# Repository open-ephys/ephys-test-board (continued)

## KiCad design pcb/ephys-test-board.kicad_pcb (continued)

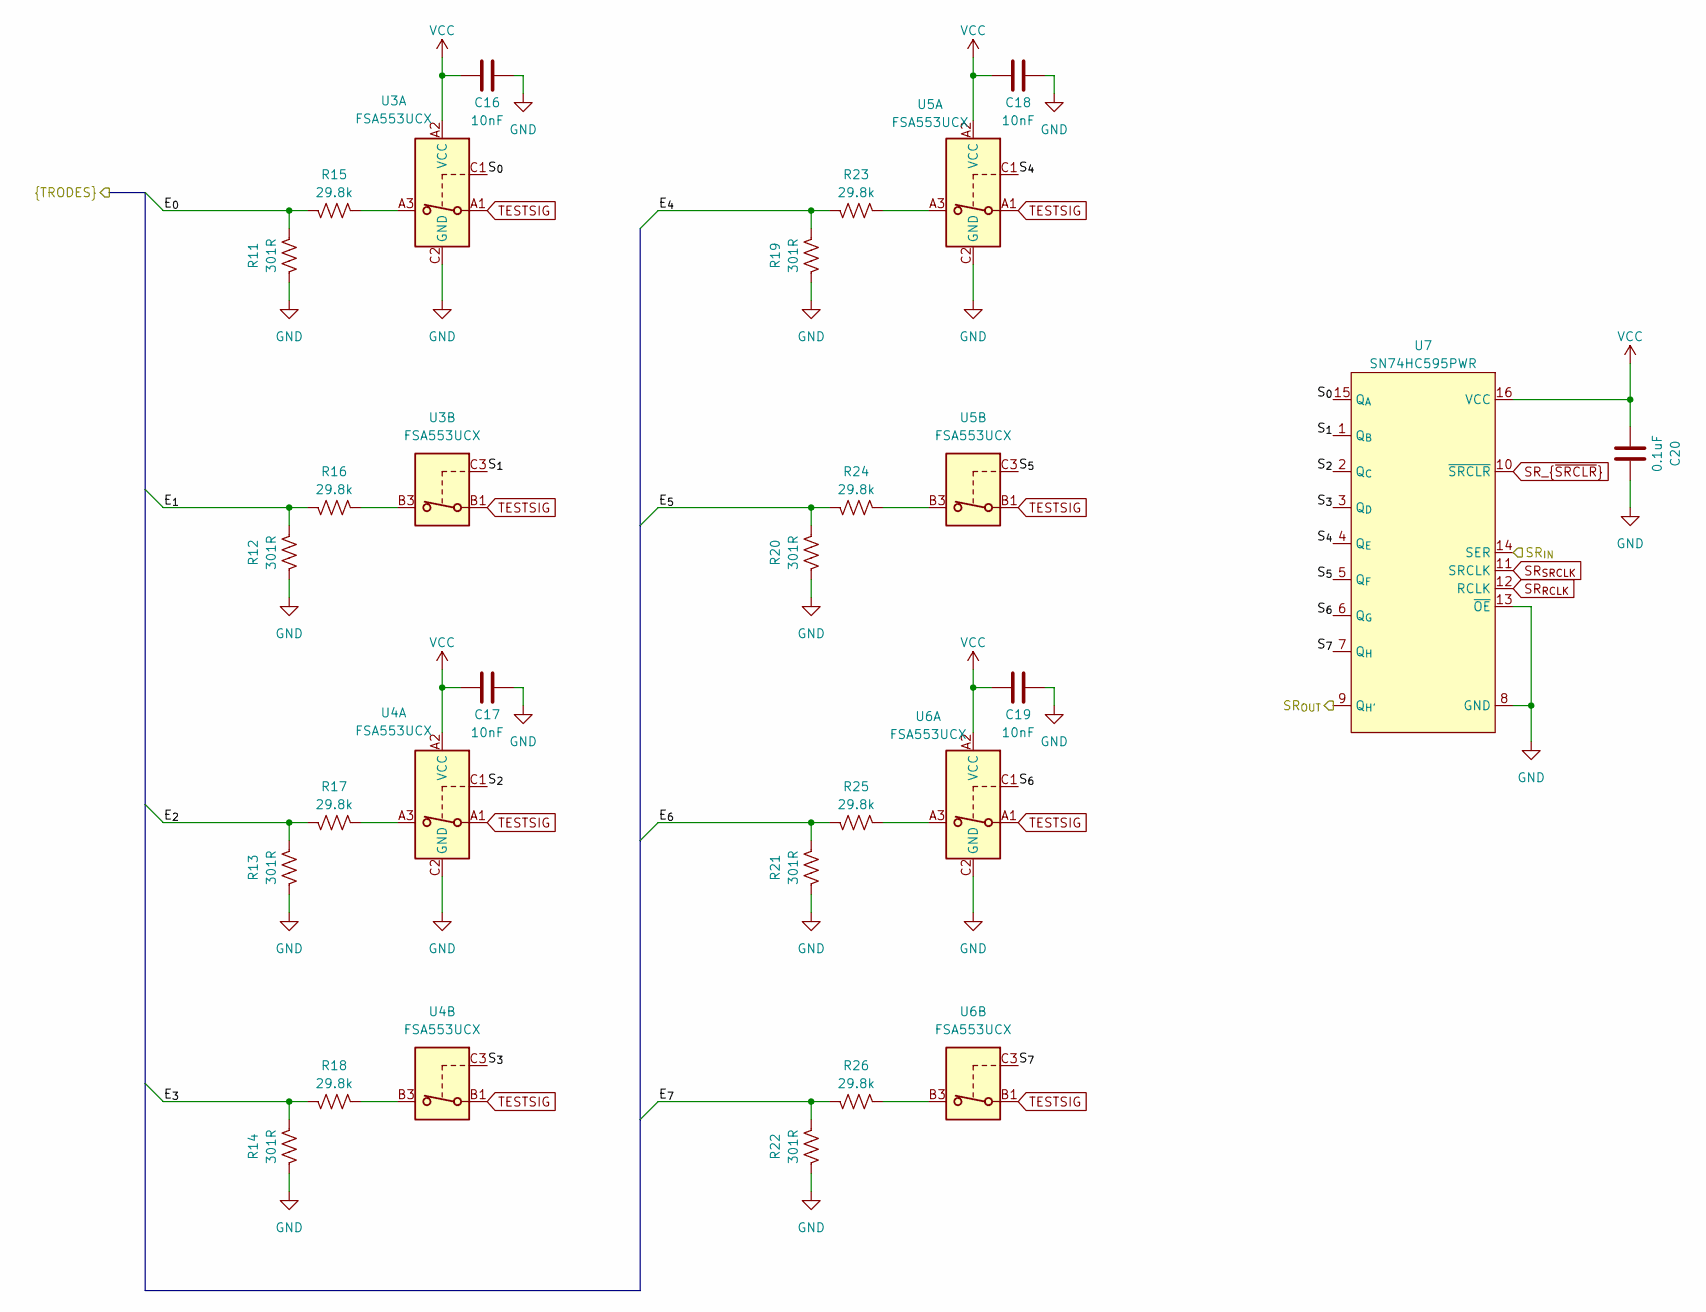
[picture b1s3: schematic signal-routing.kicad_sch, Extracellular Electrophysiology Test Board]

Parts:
C16, C17, C18, C19: 10nF; C_0402_1005Metric; Voltage 50V; MPN GRM155R71E103KA01D; LCSC C60133
C20: 0.1uF; C_0402_1005Metric; Voltage 25V; MPN C1005X7R1E104K050BB; LCSC C105883
R11, R12, R13, R14, R19, R20, R21, R22: 301R; R_0402_1005Metric; Tolerance 0.1%; MPN RT0402BRD07301RL; LCSC C705632
R15, R16, R17, R18, R23, R24, R25, R26: 29.8k; R_0402_1005Metric; Tolerance 0.1%; MPN RN73R1ETTP2982B25; LCSC C2506693
U3, U4, U5, U6: FSA553UCX; ONSEMI_567SV_WLCSP9-3x3-1.215x1.385x0.581mm-P0.4mm; MPN FSA553UCX; LCSC C605183
U7: SN74HC595PWR; TSSOP-16_4.4x5mm_P0.65mm; MPN SN74HC595PWR; LCSC C273642

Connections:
/Headstage IO/B0.E_{0}: R11.1, R15.2; also elsewhere on the board
/Headstage IO/B0.E_{1}: R12.1, R16.2; also elsewhere on the board
/Headstage IO/B0.E_{2}: R13.1, R17.2; also elsewhere on the board
/Headstage IO/B0.E_{3}: R14.1, R18.2; also elsewhere on the board
/Headstage IO/B0.E_{4}: R19.1, R23.2; also elsewhere on the board
/Headstage IO/B0.E_{5}: R20.1, R24.2; also elsewhere on the board
/Headstage IO/B0.E_{6}: R21.1, R25.2; also elsewhere on the board
/Headstage IO/B0.E_{7}: R22.1, R26.2; also elsewhere on the board
/MCU/SR_{SER}: U7.14 (SER); also elsewhere on the board
/Signal Routing 0/SR_{OUT}: U7.9 (Q_{H'}); also elsewhere on the board
/Signal Routing 0/S_{0}: U3.C1, U7.15 (Q_{A})
/Signal Routing 0/S_{1}: U3.C3, U7.1 (Q_{B})
/Signal Routing 0/S_{2}: U4.C1, U7.2 (Q_{C})
/Signal Routing 0/S_{3}: U4.C3, U7.3 (Q_{D})
/Signal Routing 0/S_{4}: U5.C1, U7.4 (Q_{E})
/Signal Routing 0/S_{5}: U5.C3, U7.5 (Q_{F})
/Signal Routing 0/S_{6}: U6.C1, U7.6 (Q_{G})
/Signal Routing 0/S_{7}: U6.C3, U7.7 (Q_{H})
GND: C16.2, C17.2, C18.2, C19.2, C20.2, R11.2, R12.2, R13.2, R14.2, R19.2, R20.2, R21.2, R22.2, U3.C2 (GND), U4.C2 (GND), U5.C2 (GND), U6.C2 (GND), U7.8 (GND), U7.13 (~OE); also elsewhere on the board
unnamed: R15.1, U3.A3
unnamed: R16.1, U3.B3
unnamed: R17.1, U4.A3
unnamed: R18.1, U4.B3
unnamed: R23.1, U5.A3
unnamed: R24.1, U5.B3
unnamed: R25.1, U6.A3
unnamed: R26.1, U6.B3
SR_{RCLK}: U7.12 (RCLK); also elsewhere on the board
SR_{SRCLK}: U7.11 (SRCLK); also elsewhere on the board
SR_{~SRCLR}: U7.10 (~SRCLR); also elsewhere on the board
TESTSIG: U3.A1, U3.B1, U4.A1, U4.B1, U5.A1, U5.B1, U6.A1, U6.B1; also elsewhere on the board
VCC: C16.1, C17.1, C18.1, C19.1, C20.1, U3.A2 (VCC), U4.A2 (VCC), U5.A2 (VCC), U6.A2 (VCC), U7.16 (VCC); also elsewhere on the board

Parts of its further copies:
C21, C22, C23, C24, C26, C27, C28, C29, C31, C32, C33, C34, C36, C37, C38, C39, C41, C42, C43, C44, C46, C47, C48, C49, C51, C52, C53, C54, C56, C57, C58, C59, C61, C62, C63, C64, C66, C67, C68, C69, C71, C72, C73, C74, C76, C77, C78, C79, C81, C82, C83, C84, C86, C87, C88, C89, C91, C92, C93, C94: 10nF; C_0402_1005Metric; Voltage 50V; MPN GRM155R71E103KA01D; LCSC C60133
C25, C30, C35, C40, C45, C50, C55, C60, C65, C70, C75, C80, C85, C90, C95: 0.1uF; C_0402_1005Metric; Voltage 25V; MPN C1005X7R1E104K050BB; LCSC C105883
R27, R28, R29, R30, R35, R36, R37, R38, R43, R44, R45, R46, R51, R52, R53, R54, R59, R60, R61, R62, R67, R68, R69, R70, R75, R76, R77, R78, R83, R84, R85, R86, R91, R92, R93, R94, R99, R100, R101, R102, R107, R108, R109, R110, R115, R116, R117, R118, R123, R124, R125, R126, R131, R132, R133, R134, R139, R140, R141, R142, R147, R148, R149, R150, R155, R156, R157, R158, R163, R164, R165, R166, R171, R172, R173, R174, R179, R180, R181, R182, R187, R188, R189, R190, R195, R196, R197, R198, R203, R204, R205, R206, R211, R212, R213, R214, R219, R220, R221, R222, R227, R228, R229, R230, R235, R236, R237, R238, R243, R244, R245, R246, R251, R252, R253, R254, R259, R260, R261, R262: 301R; R_0402_1005Metric; Tolerance 0.1%; MPN RT0402BRD07301RL; LCSC C705632
R31, R32, R33, R34, R39, R40, R41, R42, R47, R48, R49, R50, R55, R56, R57, R58, R63, R64, R65, R66, R71, R72, R73, R74, R79, R80, R81, R82, R87, R88, R89, R90, R95, R96, R97, R98, R103, R104, R105, R106, R111, R112, R113, R114, R119, R120, R121, R122, R127, R128, R129, R130, R135, R136, R137, R138, R143, R144, R145, R146, R151, R152, R153, R154, R159, R160, R161, R162, R167, R168, R169, R170, R175, R176, R177, R178, R183, R184, R185, R186, R191, R192, R193, R194, R199, R200, R201, R202, R207, R208, R209, R210, R215, R216, R217, R218, R223, R224, R225, R226, R231, R232, R233, R234, R239, R240, R241, R242, R247, R248, R249, R250, R255, R256, R257, R258, R263, R264, R265, R266: 29.8k; R_0402_1005Metric; Tolerance 0.1%; MPN RN73R1ETTP2982B25; LCSC C2506693
U8, U9, U10, U11, U13, U14, U15, U16, U18, U19, U20, U21, U23, U24, U25, U26, U28, U29, U30, U31, U33, U34, U35, U36, U38, U39, U40, U41, U43, U44, U45, U46, U48, U49, U50, U51, U53, U54, U55, U56, U58, U59, U60, U61, U63, U64, U65, U66, U68, U69, U70, U71, U73, U74, U75, U76, U78, U79, U80, U81: FSA553UCX; ONSEMI_567SV_WLCSP9-3x3-1.215x1.385x0.581mm-P0.4mm; MPN FSA553UCX; LCSC C605183
U12, U17, U22, U27, U32, U37, U42, U47, U52, U57, U62, U67, U72, U77, U82: SN74HC595PWR; TSSOP-16_4.4x5mm_P0.65mm; MPN SN74HC595PWR; LCSC C273642

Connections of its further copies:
/Headstage IO/B1.E_{0}: R27.1, R31.2; also elsewhere on the board
/Headstage IO/B1.E_{1}: R28.1, R32.2; also elsewhere on the board
/Headstage IO/B1.E_{2}: R29.1, R33.2; also elsewhere on the board
/Headstage IO/B1.E_{3}: R30.1, R34.2; also elsewhere on the board
/Headstage IO/B1.E_{4}: R35.1, R39.2; also elsewhere on the board
/Headstage IO/B1.E_{5}: R36.1, R40.2; also elsewhere on the board
/Headstage IO/B1.E_{6}: R37.1, R41.2; also elsewhere on the board
/Headstage IO/B1.E_{7}: R38.1, R42.2; also elsewhere on the board
/Headstage IO/B2.E_{0}: R43.1, R47.2; also elsewhere on the board
/Headstage IO/B2.E_{1}: R44.1, R48.2; also elsewhere on the board
/Headstage IO/B2.E_{2}: R45.1, R49.2; also elsewhere on the board
/Headstage IO/B2.E_{3}: R46.1, R50.2; also elsewhere on the board
/Headstage IO/B2.E_{4}: R51.1, R55.2; also elsewhere on the board
/Headstage IO/B2.E_{5}: R52.1, R56.2; also elsewhere on the board
/Headstage IO/B2.E_{6}: R53.1, R57.2; also elsewhere on the board
/Headstage IO/B2.E_{7}: R54.1, R58.2; also elsewhere on the board
/Headstage IO/B3.E_{0}: R59.1, R63.2; also elsewhere on the board
/Headstage IO/B3.E_{1}: R60.1, R64.2; also elsewhere on the board
/Headstage IO/B3.E_{2}: R61.1, R65.2; also elsewhere on the board
/Headstage IO/B3.E_{3}: R62.1, R66.2; also elsewhere on the board
/Headstage IO/B3.E_{4}: R67.1, R71.2; also elsewhere on the board
/Headstage IO/B3.E_{5}: R68.1, R72.2; also elsewhere on the board
/Headstage IO/B3.E_{6}: R69.1, R73.2; also elsewhere on the board
/Headstage IO/B3.E_{7}: R70.1, R74.2; also elsewhere on the board
/Headstage IO/B4.E_{0}: R75.1, R79.2; also elsewhere on the board
/Headstage IO/B4.E_{1}: R76.1, R80.2; also elsewhere on the board
/Headstage IO/B4.E_{2}: R77.1, R81.2; also elsewhere on the board
/Headstage IO/B4.E_{3}: R78.1, R82.2; also elsewhere on the board
/Headstage IO/B4.E_{4}: R83.1, R87.2; also elsewhere on the board
/Headstage IO/B4.E_{5}: R84.1, R88.2; also elsewhere on the board
/Headstage IO/B4.E_{6}: R85.1, R89.2; also elsewhere on the board
/Headstage IO/B4.E_{7}: R86.1, R90.2; also elsewhere on the board
/Headstage IO/B5.E_{0}: R91.1, R95.2; also elsewhere on the board
/Headstage IO/B5.E_{1}: R92.1, R96.2; also elsewhere on the board
/Headstage IO/B5.E_{2}: R93.1, R97.2; also elsewhere on the board
/Headstage IO/B5.E_{3}: R94.1, R98.2; also elsewhere on the board
/Headstage IO/B5.E_{4}: R99.1, R103.2; also elsewhere on the board
/Headstage IO/B5.E_{5}: R100.1, R104.2; also elsewhere on the board
/Headstage IO/B5.E_{6}: R101.1, R105.2; also elsewhere on the board
/Headstage IO/B5.E_{7}: R102.1, R106.2; also elsewhere on the board
/Headstage IO/B6.E_{0}: R107.1, R111.2; also elsewhere on the board
/Headstage IO/B6.E_{1}: R108.1, R112.2; also elsewhere on the board
/Headstage IO/B6.E_{2}: R109.1, R113.2; also elsewhere on the board
/Headstage IO/B6.E_{3}: R110.1, R114.2; also elsewhere on the board
/Headstage IO/B6.E_{4}: R115.1, R119.2; also elsewhere on the board
/Headstage IO/B6.E_{5}: R116.1, R120.2; also elsewhere on the board
/Headstage IO/B6.E_{6}: R117.1, R121.2; also elsewhere on the board
/Headstage IO/B6.E_{7}: R118.1, R122.2; also elsewhere on the board
/Headstage IO/B7.E_{0}: R123.1, R127.2; also elsewhere on the board
/Headstage IO/B7.E_{1}: R124.1, R128.2; also elsewhere on the board
/Headstage IO/B7.E_{2}: R125.1, R129.2; also elsewhere on the board
/Headstage IO/B7.E_{3}: R126.1, R130.2; also elsewhere on the board
/Headstage IO/B7.E_{4}: R131.1, R135.2; also elsewhere on the board
/Headstage IO/B7.E_{5}: R132.1, R136.2; also elsewhere on the board
/Headstage IO/B7.E_{6}: R133.1, R137.2; also elsewhere on the board
/Headstage IO/B7.E_{7}: R134.1, R138.2; also elsewhere on the board
/Headstage IO/B8.E_{0}: R139.1, R143.2; also elsewhere on the board
/Headstage IO/B8.E_{1}: R140.1, R144.2; also elsewhere on the board
/Headstage IO/B8.E_{2}: R141.1, R145.2; also elsewhere on the board
/Headstage IO/B8.E_{3}: R142.1, R146.2; also elsewhere on the board
/Headstage IO/B8.E_{4}: R147.1, R151.2; also elsewhere on the board
/Headstage IO/B8.E_{5}: R148.1, R152.2; also elsewhere on the board
/Headstage IO/B8.E_{6}: R149.1, R153.2; also elsewhere on the board
/Headstage IO/B8.E_{7}: R150.1, R154.2; also elsewhere on the board
/Headstage IO/B9.E_{0}: R155.1, R159.2; also elsewhere on the board
/Headstage IO/B9.E_{1}: R156.1, R160.2; also elsewhere on the board
/Headstage IO/B9.E_{2}: R157.1, R161.2; also elsewhere on the board
/Headstage IO/B9.E_{3}: R158.1, R162.2; also elsewhere on the board
/Headstage IO/B9.E_{4}: R163.1, R167.2; also elsewhere on the board
/Headstage IO/B9.E_{5}: R164.1, R168.2; also elsewhere on the board
/Headstage IO/B9.E_{6}: R165.1, R169.2; also elsewhere on the board
/Headstage IO/B9.E_{7}: R166.1, R170.2; also elsewhere on the board
/Headstage IO/B10.E_{0}: R171.1, R175.2; also elsewhere on the board
/Headstage IO/B10.E_{1}: R172.1, R176.2; also elsewhere on the board
/Headstage IO/B10.E_{2}: R173.1, R177.2; also elsewhere on the board
/Headstage IO/B10.E_{3}: R174.1, R178.2; also elsewhere on the board
/Headstage IO/B10.E_{4}: R179.1, R183.2; also elsewhere on the board
/Headstage IO/B10.E_{5}: R180.1, R184.2; also elsewhere on the board
/Headstage IO/B10.E_{6}: R181.1, R185.2; also elsewhere on the board
/Headstage IO/B10.E_{7}: R182.1, R186.2; also elsewhere on the board
/Headstage IO/B11.E_{0}: R187.1, R191.2; also elsewhere on the board
/Headstage IO/B11.E_{1}: R188.1, R192.2; also elsewhere on the board
/Headstage IO/B11.E_{2}: R189.1, R193.2; also elsewhere on the board
/Headstage IO/B11.E_{3}: R190.1, R194.2; also elsewhere on the board
/Headstage IO/B11.E_{4}: R195.1, R199.2; also elsewhere on the board
/Headstage IO/B11.E_{5}: R196.1, R200.2; also elsewhere on the board
/Headstage IO/B11.E_{6}: R197.1, R201.2; also elsewhere on the board
/Headstage IO/B11.E_{7}: R198.1, R202.2; also elsewhere on the board
/Headstage IO/B12.E_{0}: R203.1, R207.2; also elsewhere on the board
/Headstage IO/B12.E_{1}: R204.1, R208.2; also elsewhere on the board
/Headstage IO/B12.E_{2}: R205.1, R209.2; also elsewhere on the board
/Headstage IO/B12.E_{3}: R206.1, R210.2; also elsewhere on the board
/Headstage IO/B12.E_{4}: R211.1, R215.2; also elsewhere on the board
/Headstage IO/B12.E_{5}: R212.1, R216.2; also elsewhere on the board
/Headstage IO/B12.E_{6}: R213.1, R217.2; also elsewhere on the board
/Headstage IO/B12.E_{7}: R214.1, R218.2; also elsewhere on the board
/Headstage IO/B13.E_{0}: R219.1, R223.2; also elsewhere on the board
/Headstage IO/B13.E_{1}: R220.1, R224.2; also elsewhere on the board
/Headstage IO/B13.E_{2}: R221.1, R225.2; also elsewhere on the board
/Headstage IO/B13.E_{3}: R222.1, R226.2; also elsewhere on the board
/Headstage IO/B13.E_{4}: R227.1, R231.2; also elsewhere on the board
/Headstage IO/B13.E_{5}: R228.1, R232.2; also elsewhere on the board
/Headstage IO/B13.E_{6}: R229.1, R233.2; also elsewhere on the board
/Headstage IO/B13.E_{7}: R230.1, R234.2; also elsewhere on the board
/Headstage IO/B14.E_{0}: R235.1, R239.2; also elsewhere on the board
/Headstage IO/B14.E_{1}: R236.1, R240.2; also elsewhere on the board
/Headstage IO/B14.E_{2}: R237.1, R241.2; also elsewhere on the board
/Headstage IO/B14.E_{3}: R238.1, R242.2; also elsewhere on the board
/Headstage IO/B14.E_{4}: R243.1, R247.2; also elsewhere on the board
/Headstage IO/B14.E_{5}: R244.1, R248.2; also elsewhere on the board
/Headstage IO/B14.E_{6}: R245.1, R249.2; also elsewhere on the board
/Headstage IO/B14.E_{7}: R246.1, R250.2; also elsewhere on the board
/Headstage IO/B15.E_{0}: R251.1, R255.2; also elsewhere on the board
/Headstage IO/B15.E_{1}: R252.1, R256.2; also elsewhere on the board
/Headstage IO/B15.E_{2}: R253.1, R257.2; also elsewhere on the board
/Headstage IO/B15.E_{3}: R254.1, R258.2; also elsewhere on the board
/Headstage IO/B15.E_{4}: R259.1, R263.2; also elsewhere on the board
/Headstage IO/B15.E_{5}: R260.1, R264.2; also elsewhere on the board
/Headstage IO/B15.E_{6}: R261.1, R265.2; also elsewhere on the board
/Headstage IO/B15.E_{7}: R262.1, R266.2; also elsewhere on the board
/Signal Routing 0/SR_{OUT}: U12.14 (SER); also elsewhere on the board
/Signal Routing 1/SR_{OUT}: U12.9 (Q_{H'}), U17.14 (SER)
/Signal Routing 1/S_{0}: U8.C1, U12.15 (Q_{A})
/Signal Routing 1/S_{1}: U8.C3, U12.1 (Q_{B})
/Signal Routing 1/S_{2}: U9.C1, U12.2 (Q_{C})
/Signal Routing 1/S_{3}: U9.C3, U12.3 (Q_{D})
/Signal Routing 1/S_{4}: U10.C1, U12.4 (Q_{E})
/Signal Routing 1/S_{5}: U10.C3, U12.5 (Q_{F})
/Signal Routing 1/S_{6}: U11.C1, U12.6 (Q_{G})
/Signal Routing 1/S_{7}: U11.C3, U12.7 (Q_{H})
/Signal Routing 2/SR_{OUT}: U17.9 (Q_{H'}), U22.14 (SER)
/Signal Routing 2/S_{0}: U13.C1, U17.15 (Q_{A})
/Signal Routing 2/S_{1}: U13.C3, U17.1 (Q_{B})
/Signal Routing 2/S_{2}: U14.C1, U17.2 (Q_{C})
/Signal Routing 2/S_{3}: U14.C3, U17.3 (Q_{D})
/Signal Routing 2/S_{4}: U15.C1, U17.4 (Q_{E})
/Signal Routing 2/S_{5}: U15.C3, U17.5 (Q_{F})
/Signal Routing 2/S_{6}: U16.C1, U17.6 (Q_{G})
/Signal Routing 2/S_{7}: U16.C3, U17.7 (Q_{H})
/Signal Routing 3/SR_{OUT}: U22.9 (Q_{H'}), U27.14 (SER)
/Signal Routing 3/S_{0}: U18.C1, U22.15 (Q_{A})
/Signal Routing 3/S_{1}: U18.C3, U22.1 (Q_{B})
/Signal Routing 3/S_{2}: U19.C1, U22.2 (Q_{C})
/Signal Routing 3/S_{3}: U19.C3, U22.3 (Q_{D})
/Signal Routing 3/S_{4}: U20.C1, U22.4 (Q_{E})
/Signal Routing 3/S_{5}: U20.C3, U22.5 (Q_{F})
/Signal Routing 3/S_{6}: U21.C1, U22.6 (Q_{G})
/Signal Routing 3/S_{7}: U21.C3, U22.7 (Q_{H})
/Signal Routing 4/SR_{OUT}: U27.9 (Q_{H'}), U32.14 (SER)
/Signal Routing 4/S_{0}: U23.C1, U27.15 (Q_{A})
/Signal Routing 4/S_{1}: U23.C3, U27.1 (Q_{B})
/Signal Routing 4/S_{2}: U24.C1, U27.2 (Q_{C})
/Signal Routing 4/S_{3}: U24.C3, U27.3 (Q_{D})
/Signal Routing 4/S_{4}: U25.C1, U27.4 (Q_{E})
/Signal Routing 4/S_{5}: U25.C3, U27.5 (Q_{F})
/Signal Routing 4/S_{6}: U26.C1, U27.6 (Q_{G})
/Signal Routing 4/S_{7}: U26.C3, U27.7 (Q_{H})
/Signal Routing 5/SR_{OUT}: U32.9 (Q_{H'}), U37.14 (SER)
/Signal Routing 5/S_{0}: U28.C1, U32.15 (Q_{A})
/Signal Routing 5/S_{1}: U28.C3, U32.1 (Q_{B})
/Signal Routing 5/S_{2}: U29.C1, U32.2 (Q_{C})
/Signal Routing 5/S_{3}: U29.C3, U32.3 (Q_{D})
/Signal Routing 5/S_{4}: U30.C1, U32.4 (Q_{E})
/Signal Routing 5/S_{5}: U30.C3, U32.5 (Q_{F})
/Signal Routing 5/S_{6}: U31.C1, U32.6 (Q_{G})
/Signal Routing 5/S_{7}: U31.C3, U32.7 (Q_{H})
/Signal Routing 6/SR_{OUT}: U37.9 (Q_{H'}), U42.14 (SER)
/Signal Routing 6/S_{0}: U33.C1, U37.15 (Q_{A})
/Signal Routing 6/S_{1}: U33.C3, U37.1 (Q_{B})
/Signal Routing 6/S_{2}: U34.C1, U37.2 (Q_{C})
/Signal Routing 6/S_{3}: U34.C3, U37.3 (Q_{D})
/Signal Routing 6/S_{4}: U35.C1, U37.4 (Q_{E})
/Signal Routing 6/S_{5}: U35.C3, U37.5 (Q_{F})
/Signal Routing 6/S_{6}: U36.C1, U37.6 (Q_{G})
/Signal Routing 6/S_{7}: U36.C3, U37.7 (Q_{H})
/Signal Routing 7/SR_{OUT}: U42.9 (Q_{H'}), U47.14 (SER)
/Signal Routing 7/S_{0}: U38.C1, U42.15 (Q_{A})
/Signal Routing 7/S_{1}: U38.C3, U42.1 (Q_{B})
/Signal Routing 7/S_{2}: U39.C1, U42.2 (Q_{C})
/Signal Routing 7/S_{3}: U39.C3, U42.3 (Q_{D})
/Signal Routing 7/S_{4}: U40.C1, U42.4 (Q_{E})
/Signal Routing 7/S_{5}: U40.C3, U42.5 (Q_{F})
/Signal Routing 7/S_{6}: U41.C1, U42.6 (Q_{G})
/Signal Routing 7/S_{7}: U41.C3, U42.7 (Q_{H})
/Signal Routing 8/SR_{OUT}: U47.9 (Q_{H'}), U52.14 (SER)
/Signal Routing 8/S_{0}: U43.C1, U47.15 (Q_{A})
/Signal Routing 8/S_{1}: U43.C3, U47.1 (Q_{B})
/Signal Routing 8/S_{2}: U44.C1, U47.2 (Q_{C})
/Signal Routing 8/S_{3}: U44.C3, U47.3 (Q_{D})
/Signal Routing 8/S_{4}: U45.C1, U47.4 (Q_{E})
/Signal Routing 8/S_{5}: U45.C3, U47.5 (Q_{F})
/Signal Routing 8/S_{6}: U46.C1, U47.6 (Q_{G})
/Signal Routing 8/S_{7}: U46.C3, U47.7 (Q_{H})
/Signal Routing 9/S_{0}: U48.C1, U52.15 (Q_{A})
/Signal Routing 9/S_{1}: U48.C3, U52.1 (Q_{B})
/Signal Routing 9/S_{2}: U49.C1, U52.2 (Q_{C})
/Signal Routing 9/S_{3}: U49.C3, U52.3 (Q_{D})
/Signal Routing 9/S_{4}: U50.C1, U52.4 (Q_{E})
/Signal Routing 9/S_{5}: U50.C3, U52.5 (Q_{F})
/Signal Routing 9/S_{6}: U51.C1, U52.6 (Q_{G})
/Signal Routing 9/S_{7}: U51.C3, U52.7 (Q_{H})
/Signal Routing 10/SR_{IN}: U52.9 (Q_{H'}), U57.14 (SER)
/Signal Routing 10/SR_{OUT}: U57.9 (Q_{H'}), U62.14 (SER)
/Signal Routing 10/S_{0}: U53.C1, U57.15 (Q_{A})
/Signal Routing 10/S_{1}: U53.C3, U57.1 (Q_{B})
/Signal Routing 10/S_{2}: U54.C1, U57.2 (Q_{C})
/Signal Routing 10/S_{3}: U54.C3, U57.3 (Q_{D})
/Signal Routing 10/S_{4}: U55.C1, U57.4 (Q_{E})
/Signal Routing 10/S_{5}: U55.C3, U57.5 (Q_{F})
/Signal Routing 10/S_{6}: U56.C1, U57.6 (Q_{G})
/Signal Routing 10/S_{7}: U56.C3, U57.7 (Q_{H})
/Signal Routing 11/SR_{OUT}: U62.9 (Q_{H'}), U67.14 (SER)
/Signal Routing 11/S_{0}: U58.C1, U62.15 (Q_{A})
/Signal Routing 11/S_{1}: U58.C3, U62.1 (Q_{B})
/Signal Routing 11/S_{2}: U59.C1, U62.2 (Q_{C})
/Signal Routing 11/S_{3}: U59.C3, U62.3 (Q_{D})
/Signal Routing 11/S_{4}: U60.C1, U62.4 (Q_{E})
/Signal Routing 11/S_{5}: U60.C3, U62.5 (Q_{F})
/Signal Routing 11/S_{6}: U61.C1, U62.6 (Q_{G})
/Signal Routing 11/S_{7}: U61.C3, U62.7 (Q_{H})
/Signal Routing 12/SR_{OUT}: U67.9 (Q_{H'}), U72.14 (SER)
/Signal Routing 12/S_{0}: U63.C1, U67.15 (Q_{A})
/Signal Routing 12/S_{1}: U63.C3, U67.1 (Q_{B})
/Signal Routing 12/S_{2}: U64.C1, U67.2 (Q_{C})
/Signal Routing 12/S_{3}: U64.C3, U67.3 (Q_{D})
/Signal Routing 12/S_{4}: U65.C1, U67.4 (Q_{E})
/Signal Routing 12/S_{5}: U65.C3, U67.5 (Q_{F})
/Signal Routing 12/S_{6}: U66.C1, U67.6 (Q_{G})
/Signal Routing 12/S_{7}: U66.C3, U67.7 (Q_{H})
/Signal Routing 13/SR_{OUT}: U72.9 (Q_{H'}), U77.14 (SER)
/Signal Routing 13/S_{0}: U68.C1, U72.15 (Q_{A})
/Signal Routing 13/S_{1}: U68.C3, U72.1 (Q_{B})
/Signal Routing 13/S_{2}: U69.C1, U72.2 (Q_{C})
/Signal Routing 13/S_{3}: U69.C3, U72.3 (Q_{D})
/Signal Routing 13/S_{4}: U70.C1, U72.4 (Q_{E})
/Signal Routing 13/S_{5}: U70.C3, U72.5 (Q_{F})
/Signal Routing 13/S_{6}: U71.C1, U72.6 (Q_{G})
/Signal Routing 13/S_{7}: U71.C3, U72.7 (Q_{H})
/Signal Routing 14/SR_{OUT}: U77.9 (Q_{H'}), U82.14 (SER)
/Signal Routing 14/S_{0}: U73.C1, U77.15 (Q_{A})
/Signal Routing 14/S_{1}: U73.C3, U77.1 (Q_{B})
/Signal Routing 14/S_{2}: U74.C1, U77.2 (Q_{C})
/Signal Routing 14/S_{3}: U74.C3, U77.3 (Q_{D})
/Signal Routing 14/S_{4}: U75.C1, U77.4 (Q_{E})
/Signal Routing 14/S_{5}: U75.C3, U77.5 (Q_{F})
/Signal Routing 14/S_{6}: U76.C1, U77.6 (Q_{G})
/Signal Routing 14/S_{7}: U76.C3, U77.7 (Q_{H})
/Signal Routing 15/SR_{OUT}: U82.9 (Q_{H'})
/Signal Routing 15/S_{0}: U78.C1, U82.15 (Q_{A})
/Signal Routing 15/S_{1}: U78.C3, U82.1 (Q_{B})
/Signal Routing 15/S_{2}: U79.C1, U82.2 (Q_{C})
/Signal Routing 15/S_{3}: U79.C3, U82.3 (Q_{D})
/Signal Routing 15/S_{4}: U80.C1, U82.4 (Q_{E})
/Signal Routing 15/S_{5}: U80.C3, U82.5 (Q_{F})
/Signal Routing 15/S_{6}: U81.C1, U82.6 (Q_{G})
/Signal Routing 15/S_{7}: U81.C3, U82.7 (Q_{H})
GND: C21.2, C22.2, C23.2, C24.2, C25.2, C26.2, C27.2, C28.2, C29.2, C30.2, C31.2, C32.2, C33.2, C34.2, C35.2, C36.2, C37.2, C38.2, C39.2, C40.2, C41.2, C42.2, C43.2, C44.2, C45.2, C46.2, C47.2, C48.2, C49.2, C50.2, C51.2, C52.2, C53.2, C54.2, C55.2, C56.2, C57.2, C58.2, C59.2, C60.2, C61.2, C62.2, C63.2, C64.2, C65.2, C66.2, C67.2, C68.2, C69.2, C70.2, C71.2, C72.2, C73.2, C74.2, C75.2, C76.2, C77.2, C78.2, C79.2, C80.2, C81.2, C82.2, C83.2, C84.2, C85.2, C86.2, C87.2, C88.2, C89.2, C90.2, C91.2, C92.2, C93.2, C94.2, C95.2, R27.2, R28.2, R29.2, R30.2, R35.2, R36.2, R37.2, R38.2, R43.2, R44.2, R45.2, R46.2, R51.2, R52.2, R53.2, R54.2, R59.2, R60.2, R61.2, R62.2, R67.2, R68.2, R69.2, R70.2, R75.2, R76.2, R77.2, R78.2, R83.2, R84.2, R85.2, R86.2, R91.2, R92.2, R93.2, R94.2, R99.2, R100.2, R101.2, R102.2, R107.2, R108.2, R109.2, R110.2, R115.2, R116.2, R117.2, R118.2, R123.2, R124.2, R125.2, R126.2, R131.2, R132.2, R133.2, R134.2, R139.2, R140.2, R141.2, R142.2, R147.2, R148.2, R149.2, R150.2, R155.2, R156.2, R157.2, R158.2, R163.2, R164.2, R165.2, R166.2, R171.2, R172.2, R173.2, R174.2, R179.2, R180.2, R181.2, R182.2, R187.2, R188.2, R189.2, R190.2, R195.2, R196.2, R197.2, R198.2, R203.2, R204.2, R205.2, R206.2, R211.2, R212.2, R213.2, R214.2, R219.2, R220.2, R221.2, R222.2, R227.2, R228.2, R229.2, R230.2, R235.2, R236.2, R237.2, R238.2, R243.2, R244.2, R245.2, R246.2, R251.2, R252.2, R253.2, R254.2, R259.2, R260.2, R261.2, R262.2, U8.C2 (GND), U9.C2 (GND), U10.C2 (GND), U11.C2 (GND), U12.8 (GND), U12.13 (~OE), U13.C2 (GND), U14.C2 (GND), U15.C2 (GND), U16.C2 (GND), U17.8 (GND), U17.13 (~OE), U18.C2 (GND), U19.C2 (GND), U20.C2 (GND), U21.C2 (GND), U22.8 (GND), U22.13 (~OE), U23.C2 (GND), U24.C2 (GND), U25.C2 (GND), U26.C2 (GND), U27.8 (GND), U27.13 (~OE), U28.C2 (GND), U29.C2 (GND), U30.C2 (GND), U31.C2 (GND), U32.8 (GND), U32.13 (~OE), U33.C2 (GND), U34.C2 (GND), U35.C2 (GND), U36.C2 (GND), U37.8 (GND), U37.13 (~OE), U38.C2 (GND), U39.C2 (GND), U40.C2 (GND), U41.C2 (GND), U42.8 (GND), U42.13 (~OE), U43.C2 (GND), U44.C2 (GND), U45.C2 (GND), U46.C2 (GND), U47.8 (GND), U47.13 (~OE), U48.C2 (GND), U49.C2 (GND), U50.C2 (GND), U51.C2 (GND), U52.8 (GND), U52.13 (~OE), U53.C2 (GND), U54.C2 (GND), U55.C2 (GND), U56.C2 (GND), U57.8 (GND), U57.13 (~OE), U58.C2 (GND), U59.C2 (GND), U60.C2 (GND), U61.C2 (GND), U62.8 (GND), U62.13 (~OE), U63.C2 (GND), U64.C2 (GND), U65.C2 (GND), U66.C2 (GND), U67.8 (GND), U67.13 (~OE), U68.C2 (GND), U69.C2 (GND), U70.C2 (GND), U71.C2 (GND), U72.8 (GND), U72.13 (~OE), U73.C2 (GND), U74.C2 (GND), U75.C2 (GND), U76.C2 (GND), U77.8 (GND), U77.13 (~OE), U78.C2 (GND), U79.C2 (GND), U80.C2 (GND), U81.C2 (GND), U82.8 (GND), U82.13 (~OE); also elsewhere on the board
unnamed: R31.1, U8.A3
unnamed: R32.1, U8.B3
unnamed: R33.1, U9.A3
unnamed: R34.1, U9.B3
unnamed: R39.1, U10.A3
unnamed: R40.1, U10.B3
unnamed: R41.1, U11.A3
unnamed: R42.1, U11.B3
unnamed: R47.1, U13.A3
unnamed: R48.1, U13.B3
unnamed: R49.1, U14.A3
unnamed: R50.1, U14.B3
unnamed: R55.1, U15.A3
unnamed: R56.1, U15.B3
unnamed: R57.1, U16.A3
unnamed: R58.1, U16.B3
unnamed: R63.1, U18.A3
unnamed: R64.1, U18.B3
unnamed: R65.1, U19.A3
unnamed: R66.1, U19.B3
unnamed: R71.1, U20.A3
unnamed: R72.1, U20.B3
unnamed: R73.1, U21.A3
unnamed: R74.1, U21.B3
unnamed: R79.1, U23.A3
unnamed: R80.1, U23.B3
unnamed: R81.1, U24.A3
unnamed: R82.1, U24.B3
unnamed: R87.1, U25.A3
unnamed: R88.1, U25.B3
unnamed: R89.1, U26.A3
unnamed: R90.1, U26.B3
unnamed: R95.1, U28.A3
unnamed: R96.1, U28.B3
unnamed: R97.1, U29.A3
unnamed: R98.1, U29.B3
unnamed: R103.1, U30.A3
unnamed: R104.1, U30.B3
unnamed: R105.1, U31.A3
unnamed: R106.1, U31.B3
unnamed: R111.1, U33.A3
unnamed: R112.1, U33.B3
unnamed: R113.1, U34.A3
unnamed: R114.1, U34.B3
unnamed: R119.1, U35.A3
unnamed: R120.1, U35.B3
unnamed: R121.1, U36.A3
unnamed: R122.1, U36.B3
unnamed: R127.1, U38.A3
unnamed: R128.1, U38.B3
unnamed: R129.1, U39.A3
unnamed: R130.1, U39.B3
unnamed: R135.1, U40.A3
unnamed: R136.1, U40.B3
unnamed: R137.1, U41.A3
unnamed: R138.1, U41.B3
unnamed: R143.1, U43.A3
unnamed: R144.1, U43.B3
unnamed: R145.1, U44.A3
unnamed: R146.1, U44.B3
unnamed: R151.1, U45.A3
unnamed: R152.1, U45.B3
unnamed: R153.1, U46.A3
unnamed: R154.1, U46.B3
unnamed: R159.1, U48.A3
unnamed: R160.1, U48.B3
unnamed: R161.1, U49.A3
unnamed: R162.1, U49.B3
unnamed: R167.1, U50.A3
unnamed: R168.1, U50.B3
unnamed: R169.1, U51.A3
unnamed: R170.1, U51.B3
unnamed: R175.1, U53.A3
unnamed: R176.1, U53.B3
unnamed: R177.1, U54.A3
unnamed: R178.1, U54.B3
unnamed: R183.1, U55.A3
unnamed: R184.1, U55.B3
unnamed: R185.1, U56.A3
unnamed: R186.1, U56.B3
unnamed: R191.1, U58.A3
unnamed: R192.1, U58.B3
unnamed: R193.1, U59.A3
unnamed: R194.1, U59.B3
unnamed: R199.1, U60.A3
unnamed: R200.1, U60.B3
unnamed: R201.1, U61.A3
unnamed: R202.1, U61.B3
unnamed: R207.1, U63.A3
unnamed: R208.1, U63.B3
unnamed: R209.1, U64.A3
unnamed: R210.1, U64.B3
unnamed: R215.1, U65.A3
unnamed: R216.1, U65.B3
unnamed: R217.1, U66.A3
unnamed: R218.1, U66.B3
unnamed: R223.1, U68.A3
unnamed: R224.1, U68.B3
unnamed: R225.1, U69.A3
unnamed: R226.1, U69.B3
unnamed: R231.1, U70.A3
unnamed: R232.1, U70.B3
unnamed: R233.1, U71.A3
unnamed: R234.1, U71.B3
unnamed: R239.1, U73.A3
unnamed: R240.1, U73.B3
unnamed: R241.1, U74.A3
unnamed: R242.1, U74.B3
unnamed: R247.1, U75.A3
unnamed: R248.1, U75.B3
unnamed: R249.1, U76.A3
unnamed: R250.1, U76.B3
unnamed: R255.1, U78.A3
unnamed: R256.1, U78.B3
unnamed: R257.1, U79.A3
unnamed: R258.1, U79.B3
unnamed: R263.1, U80.A3
unnamed: R264.1, U80.B3
unnamed: R265.1, U81.A3
unnamed: R266.1, U81.B3
SR_{RCLK}: U12.12 (RCLK), U17.12 (RCLK), U22.12 (RCLK), U27.12 (RCLK), U32.12 (RCLK), U37.12 (RCLK), U42.12 (RCLK), U47.12 (RCLK), U52.12 (RCLK), U57.12 (RCLK), U62.12 (RCLK), U67.12 (RCLK), U72.12 (RCLK), U77.12 (RCLK), U82.12 (RCLK); also elsewhere on the board
SR_{SRCLK}: U12.11 (SRCLK), U17.11 (SRCLK), U22.11 (SRCLK), U27.11 (SRCLK), U32.11 (SRCLK), U37.11 (SRCLK), U42.11 (SRCLK), U47.11 (SRCLK), U52.11 (SRCLK), U57.11 (SRCLK), U62.11 (SRCLK), U67.11 (SRCLK), U72.11 (SRCLK), U77.11 (SRCLK), U82.11 (SRCLK); also elsewhere on the board
SR_{~SRCLR}: U12.10 (~SRCLR), U17.10 (~SRCLR), U22.10 (~SRCLR), U27.10 (~SRCLR), U32.10 (~SRCLR), U37.10 (~SRCLR), U42.10 (~SRCLR), U47.10 (~SRCLR), U52.10 (~SRCLR), U57.10 (~SRCLR), U62.10 (~SRCLR), U67.10 (~SRCLR), U72.10 (~SRCLR), U77.10 (~SRCLR), U82.10 (~SRCLR); also elsewhere on the board
TESTSIG: U8.A1, U8.B1, U9.A1, U9.B1, U10.A1, U10.B1, U11.A1, U11.B1, U13.A1, U13.B1, U14.A1, U14.B1, U15.A1, U15.B1, U16.A1, U16.B1, U18.A1, U18.B1, U19.A1, U19.B1, U20.A1, U20.B1, U21.A1, U21.B1, U23.A1, U23.B1, U24.A1, U24.B1, U25.A1, U25.B1, U26.A1, U26.B1, U28.A1, U28.B1, U29.A1, U29.B1, U30.A1, U30.B1, U31.A1, U31.B1, U33.A1, U33.B1, U34.A1, U34.B1, U35.A1, U35.B1, U36.A1, U36.B1, U38.A1, U38.B1, U39.A1, U39.B1, U40.A1, U40.B1, U41.A1, U41.B1, U43.A1, U43.B1, U44.A1, U44.B1, U45.A1, U45.B1, U46.A1, U46.B1, U48.A1, U48.B1, U49.A1, U49.B1, U50.A1, U50.B1, U51.A1, U51.B1, U53.A1, U53.B1, U54.A1, U54.B1, U55.A1, U55.B1, U56.A1, U56.B1, U58.A1, U58.B1, U59.A1, U59.B1, U60.A1, U60.B1, U61.A1, U61.B1, U63.A1, U63.B1, U64.A1, U64.B1, U65.A1, U65.B1, U66.A1, U66.B1, U68.A1, U68.B1, U69.A1, U69.B1, U70.A1, U70.B1, U71.A1, U71.B1, U73.A1, U73.B1, U74.A1, U74.B1, U75.A1, U75.B1, U76.A1, U76.B1, U78.A1, U78.B1, U79.A1, U79.B1, U80.A1, U80.B1, U81.A1, U81.B1; also elsewhere on the board
VCC: C21.1, C22.1, C23.1, C24.1, C25.1, C26.1, C27.1, C28.1, C29.1, C30.1, C31.1, C32.1, C33.1, C34.1, C35.1, C36.1, C37.1, C38.1, C39.1, C40.1, C41.1, C42.1, C43.1, C44.1, C45.1, C46.1, C47.1, C48.1, C49.1, C50.1, C51.1, C52.1, C53.1, C54.1, C55.1, C56.1, C57.1, C58.1, C59.1, C60.1, C61.1, C62.1, C63.1, C64.1, C65.1, C66.1, C67.1, C68.1, C69.1, C70.1, C71.1, C72.1, C73.1, C74.1, C75.1, C76.1, C77.1, C78.1, C79.1, C80.1, C81.1, C82.1, C83.1, C84.1, C85.1, C86.1, C87.1, C88.1, C89.1, C90.1, C91.1, C92.1, C93.1, C94.1, C95.1, U8.A2 (VCC), U9.A2 (VCC), U10.A2 (VCC), U11.A2 (VCC), U12.16 (VCC), U13.A2 (VCC), U14.A2 (VCC), U15.A2 (VCC), U16.A2 (VCC), U17.16 (VCC), U18.A2 (VCC), U19.A2 (VCC), U20.A2 (VCC), U21.A2 (VCC), U22.16 (VCC), U23.A2 (VCC), U24.A2 (VCC), U25.A2 (VCC), U26.A2 (VCC), U27.16 (VCC), U28.A2 (VCC), U29.A2 (VCC), U30.A2 (VCC), U31.A2 (VCC), U32.16 (VCC), U33.A2 (VCC), U34.A2 (VCC), U35.A2 (VCC), U36.A2 (VCC), U37.16 (VCC), U38.A2 (VCC), U39.A2 (VCC), U40.A2 (VCC), U41.A2 (VCC), U42.16 (VCC), U43.A2 (VCC), U44.A2 (VCC), U45.A2 (VCC), U46.A2 (VCC), U47.16 (VCC), U48.A2 (VCC), U49.A2 (VCC), U50.A2 (VCC), U51.A2 (VCC), U52.16 (VCC), U53.A2 (VCC), U54.A2 (VCC), U55.A2 (VCC), U56.A2 (VCC), U57.16 (VCC), U58.A2 (VCC), U59.A2 (VCC), U60.A2 (VCC), U61.A2 (VCC), U62.16 (VCC), U63.A2 (VCC), U64.A2 (VCC), U65.A2 (VCC), U66.A2 (VCC), U67.16 (VCC), U68.A2 (VCC), U69.A2 (VCC), U70.A2 (VCC), U71.A2 (VCC), U72.16 (VCC), U73.A2 (VCC), U74.A2 (VCC), U75.A2 (VCC), U76.A2 (VCC), U77.16 (VCC), U78.A2 (VCC), U79.A2 (VCC), U80.A2 (VCC), U81.A2 (VCC), U82.16 (VCC); also elsewhere on the board

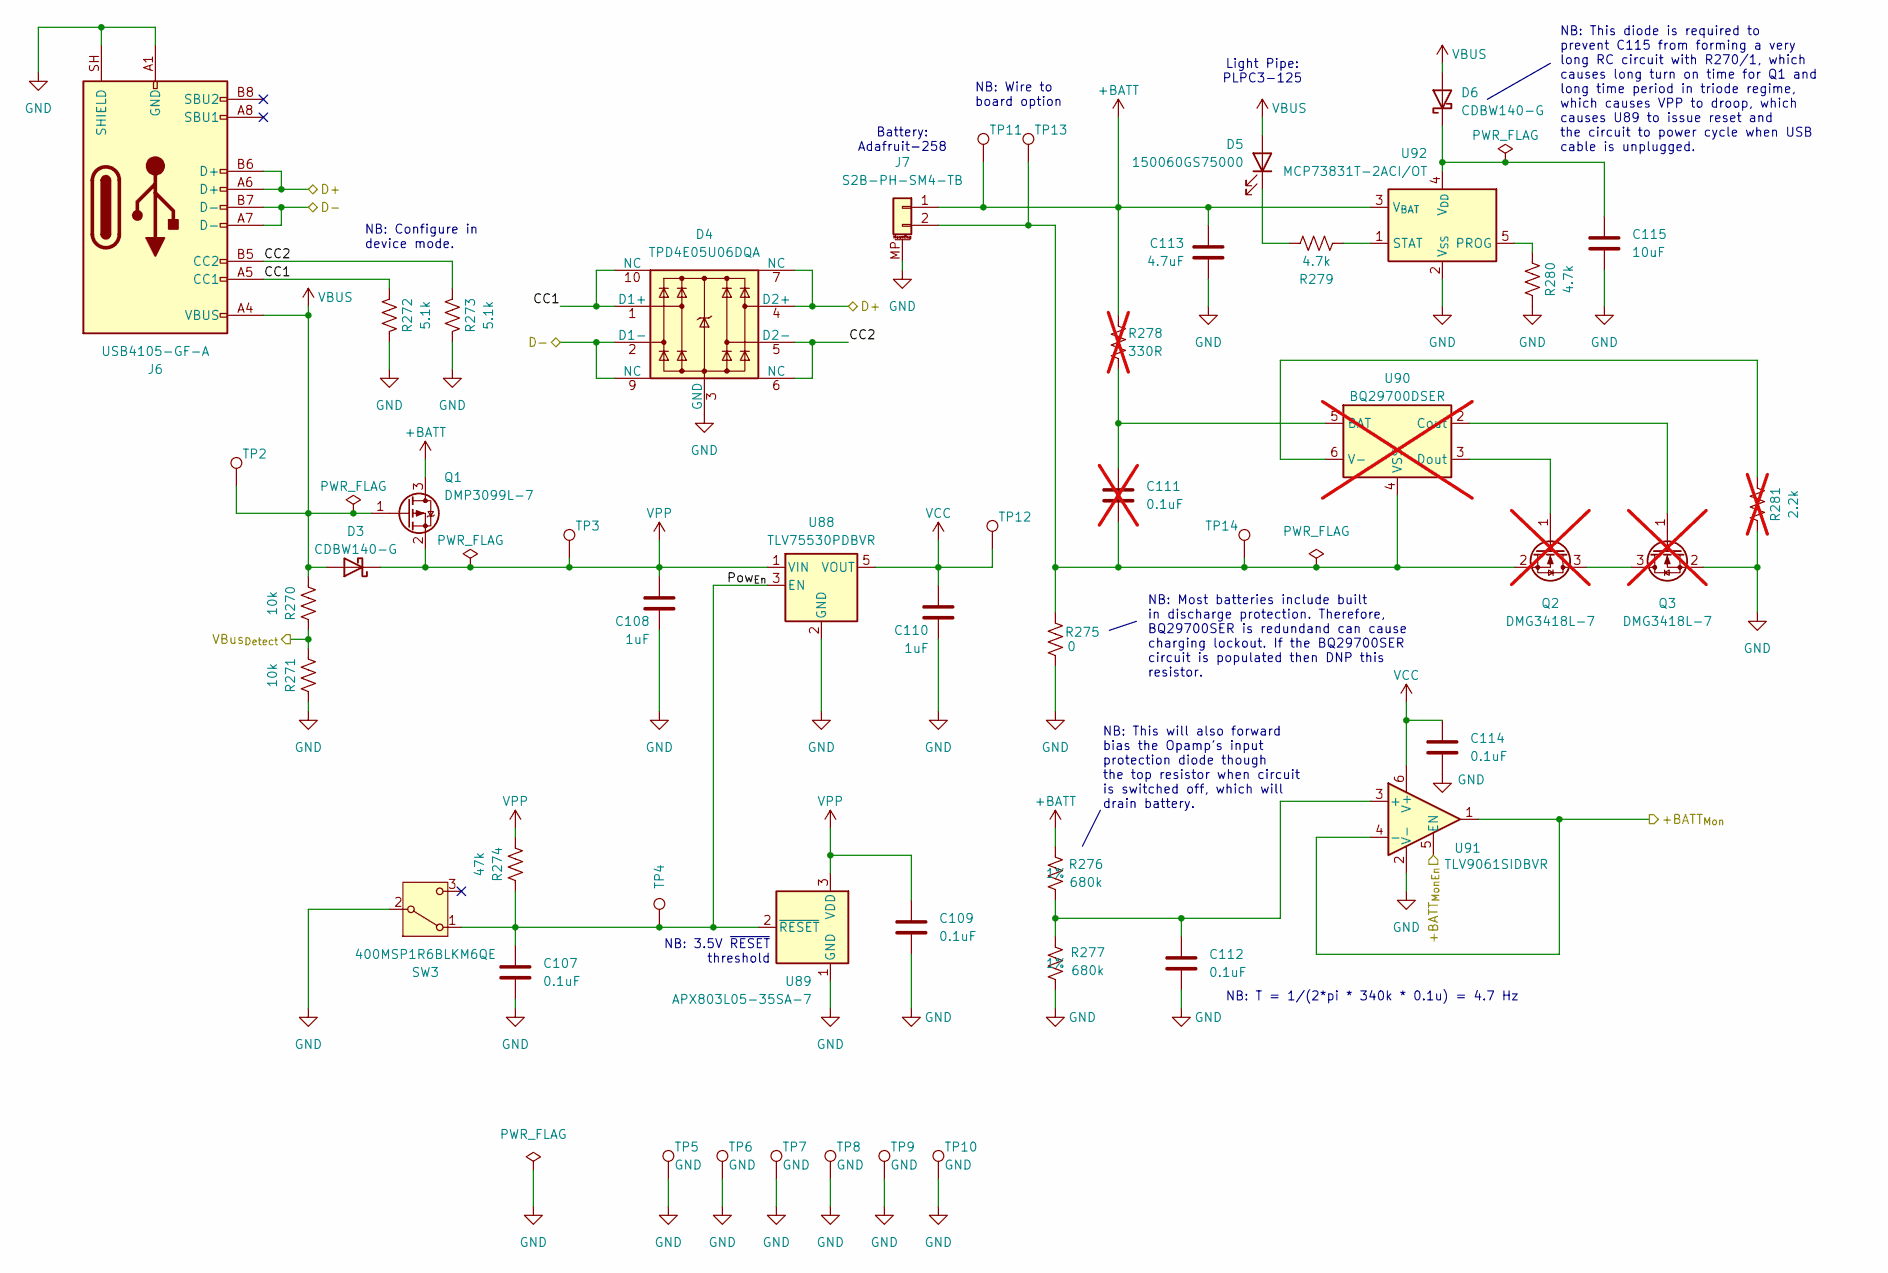
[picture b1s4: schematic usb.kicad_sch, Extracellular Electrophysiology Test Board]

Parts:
C107, C109, C112, C114: 0.1uF; C_0402_1005Metric; Voltage 25V; MPN C1005X7R1E104K050BB; LCSC C105883
C108, C110: 1uF; C_0603_1608Metric; Voltage 16V; MPN CL10A105KA8NNNC; LCSC C5673
C111: 0.1uF; C_0402_1005Metric; Voltage 25V; MPN C1005X7R1E104K050BB; not fitted
C113: 4.7uF; C_1206_3216Metric; Voltage 16V; MPN CL31B475KOHNNNE; LCSC C51205
C115: 10uF; C_1206_3216Metric; Voltage 16V; MPN CL31B106KBHNNNE; LCSC C13585
D3, D6: CDBW140-G; D_SOD-123; MPN CDBW140-G; LCSC C82544
D4: TPD4E05U06DQA; USON-10_2.5x1.0mm_P0.5mm; MPN TPD4E05U06DQAR; LCSC C138714
D5: 150060GS75000; LED_0603_1608Metric; MPN 150060GS75000; LCSC C916074
J6: USB4105-GF-A; USB_C_Receptacle_GCT_USB4105-xx-A_16P_TopMnt_Horizontal; MPN USB4105-GF-A; LCSC C5184243
J7: S2B-PH-SM4-TB; JST_PH_S2B-PH-SM4-TB_1x02-1MP_P2.00mm_Horizontal; MPN S2B-PH-SM4-TB; LCSC C295747
Q1: DMP3099L-7; SOT-23; MPN DMP3099L-7; LCSC C155244
Q2, Q3: DMG3418L-7; SOT-23; MPN DMG3418L-7; not fitted
R270, R271: 10k; R_0402_1005Metric; MPN CRCW040210K0FKED; LCSC C60490
R272, R273: 5.1k; R_0402_1005Metric; MPN ERJ-2RKF5101X; LCSC C105872
R274: 47k; R_0402_1005Metric; MPN ERJ-2RKF4702X; LCSC C93943
R275: 0; R_0402_1005Metric; MPN RC0402JR-070RL; LCSC C106231
R276, R277: 680k; R_0402_1005Metric; Tolerance 1%; MPN RC0402FR-13680KL; LCSC C2909377
R278: 330R; R_0603_1608Metric; MPN CRCW0603330RFKEAC; not fitted
R279, R280: 4.7k; R_0402_1005Metric; MPN ERJ-2RKF4701X; LCSC C105871
R281: 2.2k; R_0402_1005Metric; MPN ERJ-2RKF2201X; not fitted
SW3: 400MSP1R6BLKM6QE; ESWITCH_400MSPxR6xxxM6xE; MPN 400MSP1R6BLKM6QE; LCSC C6105831
TP2, TP3, TP4, TP5, TP6, TP7, TP8, TP9, TP10, TP14: GND; TestPoint_Pad_D2.0mm
TP11, TP13: TestPoint_THTPad_D3.0mm_Drill1.5mm
TP12: VCC; TestPoint_Pad_D2.0mm
U88: TLV75530PDBVR; SOT-23-5; MPN TLV75530PDBVR; LCSC C51118
U89: APX803L05-35SA-7; SOT-23; MPN APX803L05-35SA-7; LCSC C2067919
U90: BQ29700DSER; WSON-6_1.5x1.5mm_P0.5mm; MPN BQ29700DSER; not fitted
U91: TLV9061SIDBVR; SOT-23-6; MPN TLV9061SIDBVR; LCSC C2058350
U92: MCP73831T-2ACI/OT; SOT-23-5; MPN MCP73831T-2ACI/OT; LCSC C424093

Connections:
+BATT: C113.1, J7.1, Q1.3 (D), R276.1, R278.2, TP11.1 (1_1), U92.3 (V_{BAT})
/MCU/+BATT_{MonEn}: U91.5 (EN); also elsewhere on the board
/MCU/+BATT_{Mon}: U91.1, U91.4 (-); also elsewhere on the board
/MCU/D+: D4.4 (D2+), D4.7 (NC), J6.A6 (D+), J6.B6 (D+); also elsewhere on the board
/MCU/D-: D4.2 (D1-), D4.9 (NC), J6.A7 (D-), J6.B7 (D-); also elsewhere on the board
/MCU/VBus_{Detect}: R270.2, R271.1; also elsewhere on the board
/USB/CC1: D4.1 (D1+), D4.10 (NC), J6.A5 (CC1), R272.1
/USB/CC2: D4.5 (D2-), D4.6 (NC), J6.B5 (CC2), R273.1
/USB/Pow_{En}: C107.1, R274.2, SW3.1 (A), TP4.1 (1_1), U88.3 (EN), U89.2 (~RESET)
GND: C107.2, C108.2, C109.2, C110.2, C112.2, C113.2, C114.2, C115.2, D4.3 (GND), D4.8 (GND), J6.A1 (GND), J6.A12 (GND), J6.B1 (GND), J6.B12 (GND), J6.SH (SHIELD), J7.MP (MountPin), Q3.2 (S), R271.2, R272.2, R273.2, R275.1, R277.2, R280.1, R281.1, SW3.2 (B), TP5.1 (1_1), TP6.1 (1_1), TP7.1 (1_1), TP8.1 (1_1), TP9.1 (1_1), TP10.1 (1_1), U88.2 (GND), U89.1 (GND), U91.2 (V-), U92.2 (V_{SS}); also elsewhere on the board
unnamed: D5.1 (K), R279.1
unnamed: C115.1, D6.1 (K), U92.4 (V_{DD})
unnamed: C111.2, J7.2, Q2.2 (S), R275.2, TP13.1 (1_1), TP14.1 (1_1), U90.4 (VSS)
unnamed: Q2.3 (D), Q3.3 (D)
unnamed: Q2.1 (G), U90.3 (Dout)
unnamed: Q3.1 (G), U90.2 (Cout)
unnamed: C111.1, R278.1, U90.5 (BAT)
unnamed: R281.2, U90.6 (V-)
unnamed: C112.1, R276.2, R277.1, U91.3 (+)
unnamed: R280.2, U92.5 (PROG)
unnamed: R279.2, U92.1 (STAT)
VBUS: D3.2 (A), D5.2 (A), D6.2 (A), J6.A4 (VBUS), J6.A9 (VBUS), J6.B4 (VBUS), J6.B9 (VBUS), Q1.1 (G), R270.1, TP2.1 (1_1)
VCC: C110.1, C114.1, TP12.1 (1_1), U88.5 (VOUT), U91.6 (V+); also elsewhere on the board
VPP: C108.1, C109.1, D3.1 (K), Q1.2 (S), R274.1, TP3.1 (1_1), U88.1 (VIN), U89.3 (VDD)

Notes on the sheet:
NB: This will also forward bias the Opamp's input protection diode though the top resistor when circuit is switched off, which will drain battery.
NB: Wire to board option
NB: T = 1/(2*pi * 340k * 0.1u) = 4.7 Hz
Battery: Adafruit-258
NB: This diode is required to prevent C115 from forming a very long RC circuit with R270/1, which causes long turn on time for Q1 and long time period in triode regime, which causes VPP to droop, which causes U89 to issue reset and the circuit to power cycle when USB cable is unplugged.
NB: Configure in device mode.
NB: 3.5V ~{RESET} threshold
NB: Most batteries include built in discharge protection. Therefore, BQ29700SER is redundand can cause charging lockout. If the BQ29700SER circuit is populated then DNP this resistor.
Light Pipe: PLPC3-125
